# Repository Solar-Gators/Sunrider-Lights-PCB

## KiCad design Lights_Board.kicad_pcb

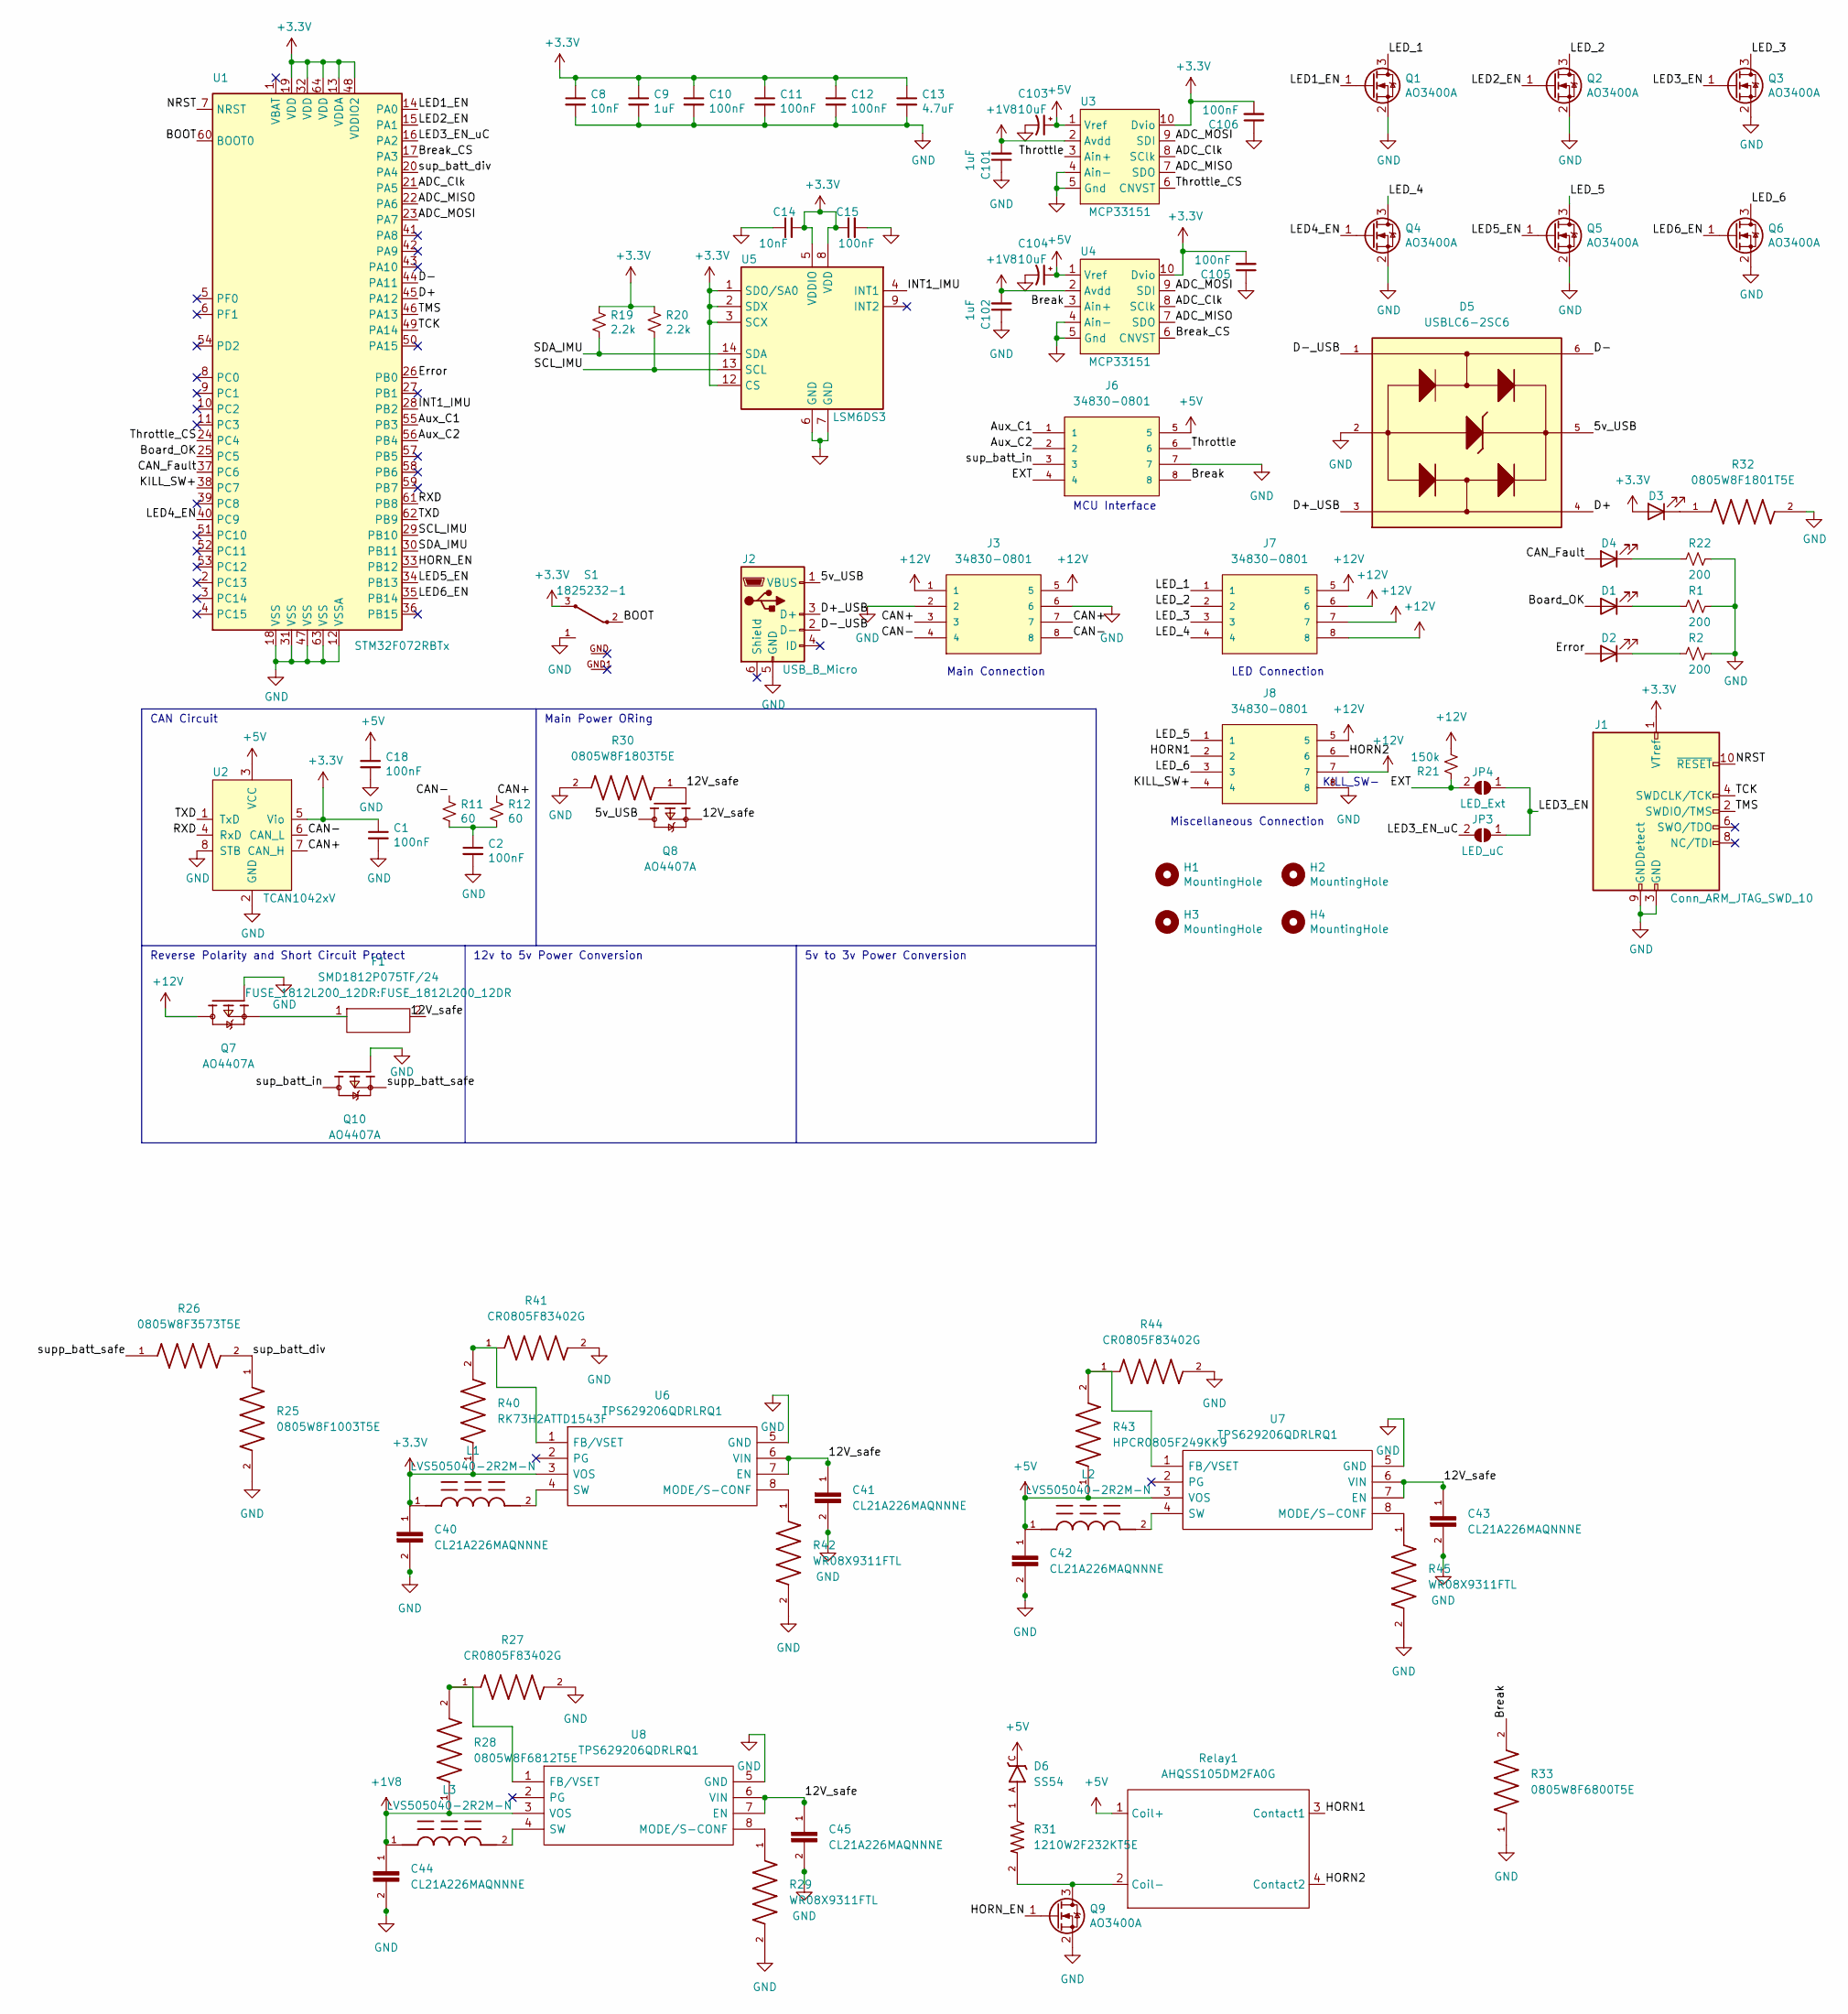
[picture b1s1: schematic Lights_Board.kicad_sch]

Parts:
C1, C2, C10, C11, C12, C15, C18, C105, C106: 100nF; C_0402_1005Metric; LCSC# C307331
C8, C14: 10nF; C_0402_1005Metric; LCSC# C15195
C9, C101, C102: 1uF; C_0402_1005Metric; LCSC# C52923
C13: 4.7uF; C_0402_1005Metric; LCSC# C23733
C40, C41, C42, C43, C44, C45: CL21A226MAQNNNE; CAPC2012X140N; JLCPCB C45783
C103, C104: 10uF; CP_EIA-3216-18_Kemet-A; LCSC# C7171
D1, D3: Board OK; LED_0805_2012Metric; LCSC# C2297
D2: Error; LED_0603_1608Metric; LCSC# C2286
D4: CAN ERR; LED_0603_1608Metric; LCSC# C2286
D5: USBLC6-2SC6; SOT95P280X145-6N; JLCPCB C5180249
D6: SS54; DO-214AC; JLCPCB C22452
F1: SMD1812P075TF/24; FUSE_1812L200_12DR; JLCPCB C12557
H1, H2, H3, H4: MountingHole; MountingHole_3.2mm_M3
J1: Conn_ARM_JTAG_SWD_10; PinHeader_2x05_P1.27mm_Vertical_SMD
J2: USB_B_Micro; USB_Micro-B_Molex_47346-0001
J3, J6, J7, J8: 34830-0801; MOLEX_34830-0801; PARTREV A2
JP3: LED_uC; SolderJumper-2_P1.3mm_Open_RoundedPad1.0x1.5mm
JP4: LED_Ext; SolderJumper-2_P1.3mm_Open_RoundedPad1.0x1.5mm
L1, L2, L3: LVS505040-2R2M-N; IND_SDR0403-2R2ML
Q1, Q2, Q3, Q4, Q5, Q6, Q9: AO3400A; SOT-23; LCSC# C20917
Q7, Q8, Q10: AO4407A; SOIC127P600X175-8N; PARTREV I
R1, R2, R22: 200; R_0603_1608Metric; LCSC# C8218
R11, R12: 60; R_0603_1608Metric
R19, R20: 2.2k; R_0603_1608Metric; LCSC# C4190
R21: 150k; R_0603_1608Metric; LCSC# C22807
R25: 0805W8F1003T5E; RESC2012X60N; JLCPCB C149504
R26: 0805W8F3573T5E; RESC2012X60N; JLCPCB C17643
R27, R41, R44: CR0805F83402G; RESC2012X60N; JLCPCB C101673
R28: 0805W8F6812T5E; RESC2012X60N; JLCPCB C17795
R29, R42, R45: WR08X9311FTL; RESC2012X60N; JLCPCB C334950
R30: 0805W8F1803T5E; RESC2012X60N; JLCPCB C17501
R31: 1210W2F232KT5E; RESC3125X65N; Tolerance 1%; JLCPCB C407202
R32: 0805W8F1801T5E; RESC2012X60N; JLCPCB C101673
R33: 0805W8F6800T5E; RESC2012X60N; JLCPCB C17798
R40: RK73H2ATTD1543F; RESC2012X60N; JLCPCB C317465
R43: HPCR0805F249KK9; RESC2012X60N; JLCPCB C365271
Relay1: AHQSS105DM2FA0G
S1: 1825232-1
U1: STM32F072RBTx; LQFP-64_10x10mm_P0.5mm
U2: TCAN1042xV; SOIC127P599X175-8N
U3, U4: MCP33151; MSOP-10_3x3mm_P0.5mm
U5: LSM6DS3; LGA-14_3x2.5mm_P0.5mm_LayoutBorder3x4y; LCSC# C784817
U6, U7, U8: TPS629206QDRLRQ1; SOTFL50P160X60-8N; Mouser Part Number 595-TPS629206QDRLRQ1

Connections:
+1V8: C44.1, C101.2, C102.2, L3.1, R28.1, U3.2 (Avdd), U4.2 (Avdd), U8.3 (VOS)
+3V3: C1.1, C8.1, C9.1, C10.1, C11.1, C12.1, C13.1, C14.2, C15.1, C40.1, C105.2, C106.2, D3.2 (A), J1.1 (VTref), L1.1, R19.1, R20.1, R40.1, S1.3, U1.13 (VDDA), U1.19 (VDD), U1.32 (VDD), U1.48 (VDDIO2), U1.64 (VDD), U2.5 (Vio), U3.10 (Dvio), U4.10 (Dvio), U5.1 (SDO/SA0), U5.2 (SDX), U5.3 (SCX), U5.5 (VDDIO), U5.8 (VDD), U5.12 (CS), U6.3 (VOS)
+5V: C18.1, C42.1, C103.1, C104.1, D6.C, J6.5, L2.1, R43.1, Relay1.1 (Coil+), U2.3 (VCC), U3.1 (Vref), U4.1 (Vref), U7.3 (VOS)
+12V: J3.1, J3.5, J7.5, J7.6, J7.7, J7.8, J8.5, J8.7, Q7.5, Q7.6, Q7.7, Q7.8, R21.2
/5v_USB: D5.5, J2.1 (VBUS), Q8.5, Q8.6, Q8.7, Q8.8
/12V_safe: C41.1, C43.1, C45.1, F1.2, Q8.1, Q8.2, Q8.3, Q8.4, R30.1, U6.6 (VIN), U6.7 (EN), U7.6 (VIN), U7.7 (EN), U8.6 (VIN), U8.7 (EN)
/ADC_Clk: U1.21 (PA5), U3.8 (SClk), U4.8 (SClk)
/ADC_MISO: U1.22 (PA6), U3.7 (SDO), U4.7 (SDO)
/ADC_MOSI: U1.23 (PA7), U3.9 (SDI), U4.9 (SDI)
/Aux_C1: J6.1, U1.55 (PB3)
/Aux_C2: J6.2, U1.56 (PB4)
/BOOT: S1.2, U1.60 (BOOT0)
/Board_OK: D1.2 (A), U1.25 (PC5)
/Break: J6.8, R33.2, U4.3 (Ain+)
/Break_CS: U1.17 (PA3), U4.6 (CNVST)
/CAN+: J3.3, J3.7, R12.1, U2.7 (CAN_H)
/CAN-: J3.4, J3.8, R11.1, U2.6 (CAN_L)
/CAN_Fault: D4.2 (A), U1.37 (PC6)
/D+: D5.4, U1.45 (PA12)
/D+_USB: D5.3, J2.3 (D+)
/D-: D5.6, U1.44 (PA11)
/D-_USB: D5.1, J2.2 (D-)
/EXT: J6.4, JP4.2 (B), R21.1
/Error: D2.2 (A), U1.26 (PB0)
/HORN1: J8.2, Relay1.3 (Contact1)
/HORN2: J8.6, Relay1.4 (Contact2)
/HORN_EN: Q9.1 (G), U1.33 (PB12)
/INT1_IMU: U1.28 (PB2), U5.4 (INT1)
/KILL_SW+: J8.4, U1.38 (PC7)
/LED1_EN: Q1.1 (G), U1.14 (PA0)
/LED2_EN: Q2.1 (G), U1.15 (PA1)
/LED3_EN: JP3.1 (A), JP4.1 (A), Q3.1 (G)
/LED3_EN_uC: JP3.2 (B), U1.16 (PA2)
/LED4_EN: Q4.1 (G), U1.40 (PC9)
/LED5_EN: Q5.1 (G), U1.34 (PB13)
/LED6_EN: Q6.1 (G), U1.35 (PB14)
/LED_1: J7.1, Q1.3 (D)
/LED_2: J7.2, Q2.3 (D)
/LED_3: J7.3, Q3.3 (D)
/LED_4: J7.4, Q4.3 (D)
/LED_5: J8.1, Q5.3 (D)
/LED_6: J8.3, Q6.3 (D)
/NRST: J1.10 (~RESET), U1.7 (NRST)
/RXD: U1.61 (PB8), U2.4 (RxD)
/SCL_IMU: R20.2, U1.29 (PB10), U5.13 (SCL)
/SDA_IMU: R19.2, U1.30 (PB11), U5.14 (SDA)
/TCK: J1.4 (SWDCLK/TCK), U1.49 (PA14)
/TMS: J1.2 (SWDIO/TMS), U1.46 (PA13)
/TXD: U1.62 (PB9), U2.1 (TxD)
/Throttle: J6.6, U3.3 (Ain+)
/Throttle_CS: U1.24 (PC4), U3.6 (CNVST)
/sup_batt_div: R25.1, R26.2, U1.20 (PA4)
/sup_batt_in: J6.3, Q10.5, Q10.6, Q10.7, Q10.8
/supp_batt_safe: Q10.1, Q10.2, Q10.3, R26.1
GND: C1.2, C2.2, C8.2, C9.2, C10.2, C11.2, C12.2, C13.2, C14.1, C15.2, C18.2, C40.2, C41.2, C42.2, C43.2, C44.2, C45.2, C101.1, C102.1, C103.2, C104.2, C105.1, C106.1, D5.2, J1.3 (GND), J1.5 (GND), J1.9 (GNDDetect), J2.5 (GND), J3.2, J3.6, J6.7, J8.8, Q1.2 (S), Q2.2 (S), Q3.2 (S), Q4.2 (S), Q5.2 (S), Q6.2 (S), Q7.4, Q9.2 (S), Q10.4, R1.1, R2.1, R22.1, R25.2, R27.2, R29.2, R30.2, R32.2, R33.1, R41.2, R42.2, R44.2, R45.2, S1.1, U1.12 (VSSA), U1.18 (VSS), U1.31 (VSS), U1.47 (VSS), U1.63 (VSS), U2.2 (GND), U2.8 (STB), U3.4 (Ain-), U3.5 (Gnd), U4.4 (Ain-), U4.5 (Gnd), U5.6 (GND), U5.7 (GND), U6.5 (GND), U7.5 (GND), U8.5 (GND)
unnamed: C2.1, R11.2, R12.2
unnamed: D1.1 (K), R1.2
unnamed: D2.1 (K), R2.2
unnamed: D3.1 (K), R32.1
unnamed: D4.1 (K), R22.2
unnamed: D6.A, R31.1
unnamed: F1.1, Q7.1, Q7.2, Q7.3
unnamed: L1.2, U6.4 (SW)
unnamed: L2.2, U7.4 (SW)
unnamed: L3.2, U8.4 (SW)
unnamed: Q9.3 (D), R31.2, Relay1.2 (Coil-)
unnamed: R27.1, R28.2, U8.1 (FB/VSET)
unnamed: R29.1, U8.8 (MODE/S-CONF)
unnamed: R40.2, R41.1, U6.1 (FB/VSET)
unnamed: R42.1, U6.8 (MODE/S-CONF)
unnamed: R43.2, R44.1, U7.1 (FB/VSET)
unnamed: R45.1, U7.8 (MODE/S-CONF)

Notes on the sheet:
MCU Interface
KILL_SW-
LED Connection
5v to 3v Power Conversion
Miscellaneous Connection
Reverse Polarity and Short Circuit Protect
12v to 5v Power Conversion
CAN Circuit
Main Connection
Main Power ORing

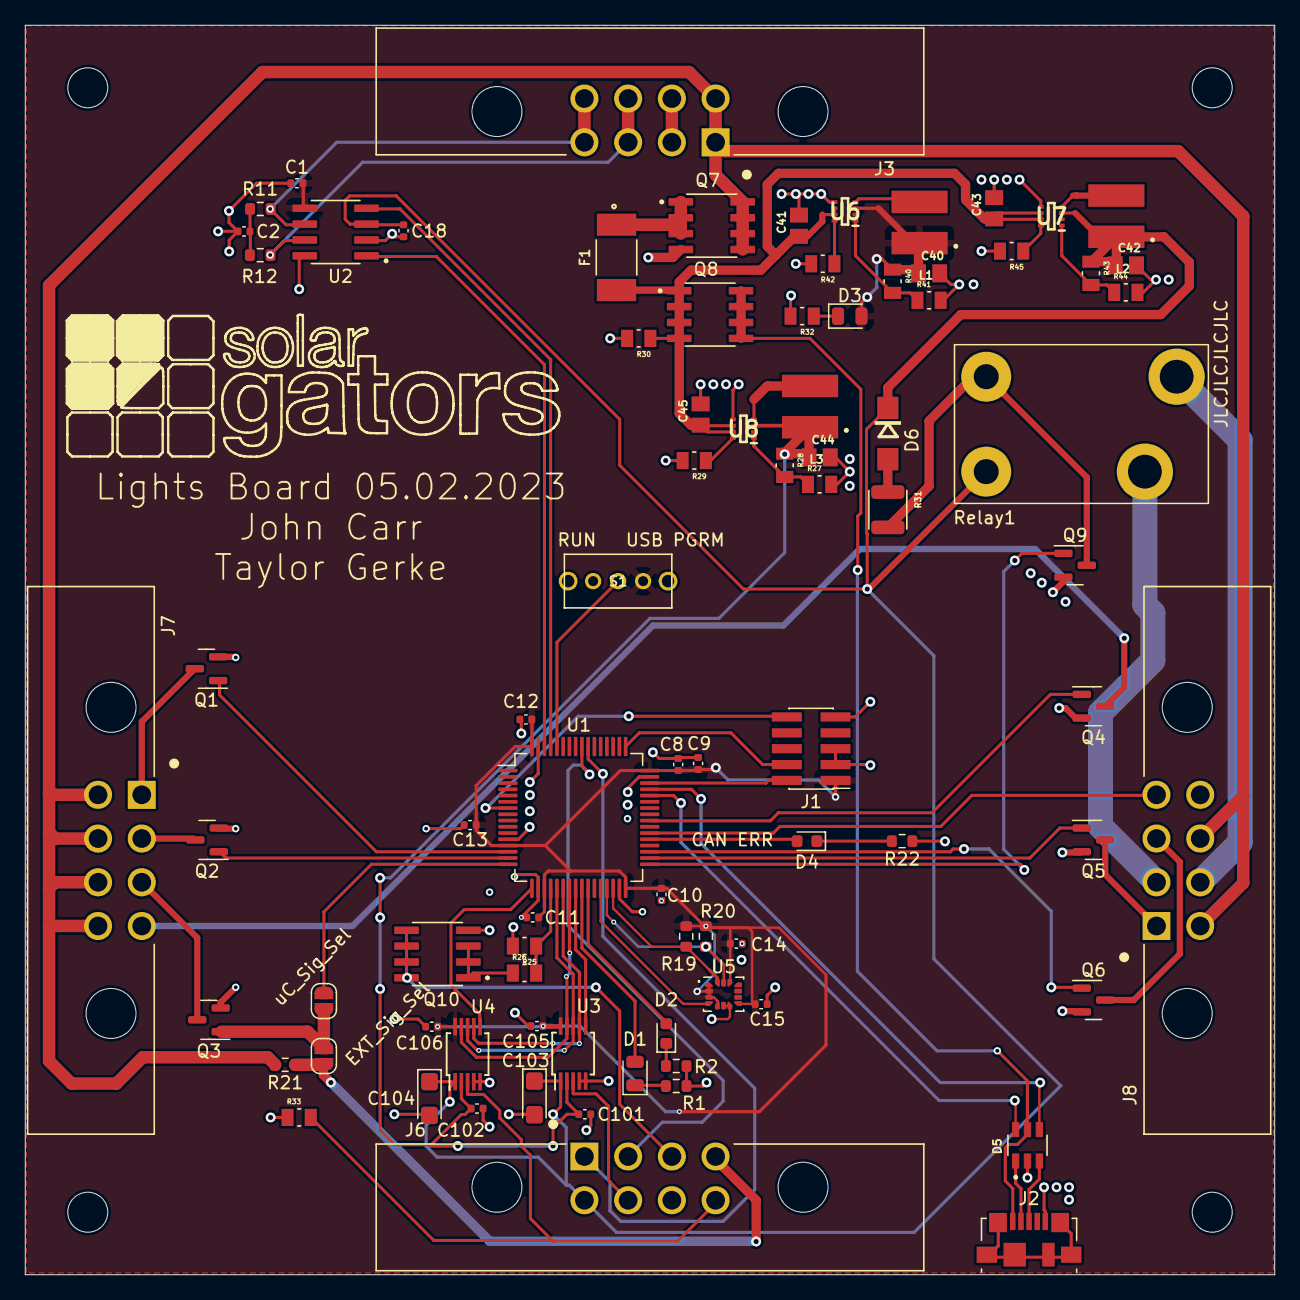
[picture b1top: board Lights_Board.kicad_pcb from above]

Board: 2 copper layers, 100.0 x 100.0 mm, 88 parts (0 on the bottom side), 72 nets.

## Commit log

2023-01-31 Initial Commit
    Known Issues:
    5V LDO ADJ pin must be grounded
    Scrutineers do not like MOSFET. Must be switched to relay instead.
    5V power mux does not work and must be replaced
2023-09-11 FSGP 2023 Lights Hardware
    Final PCB revision used for Sunrider at FSGP 2023
